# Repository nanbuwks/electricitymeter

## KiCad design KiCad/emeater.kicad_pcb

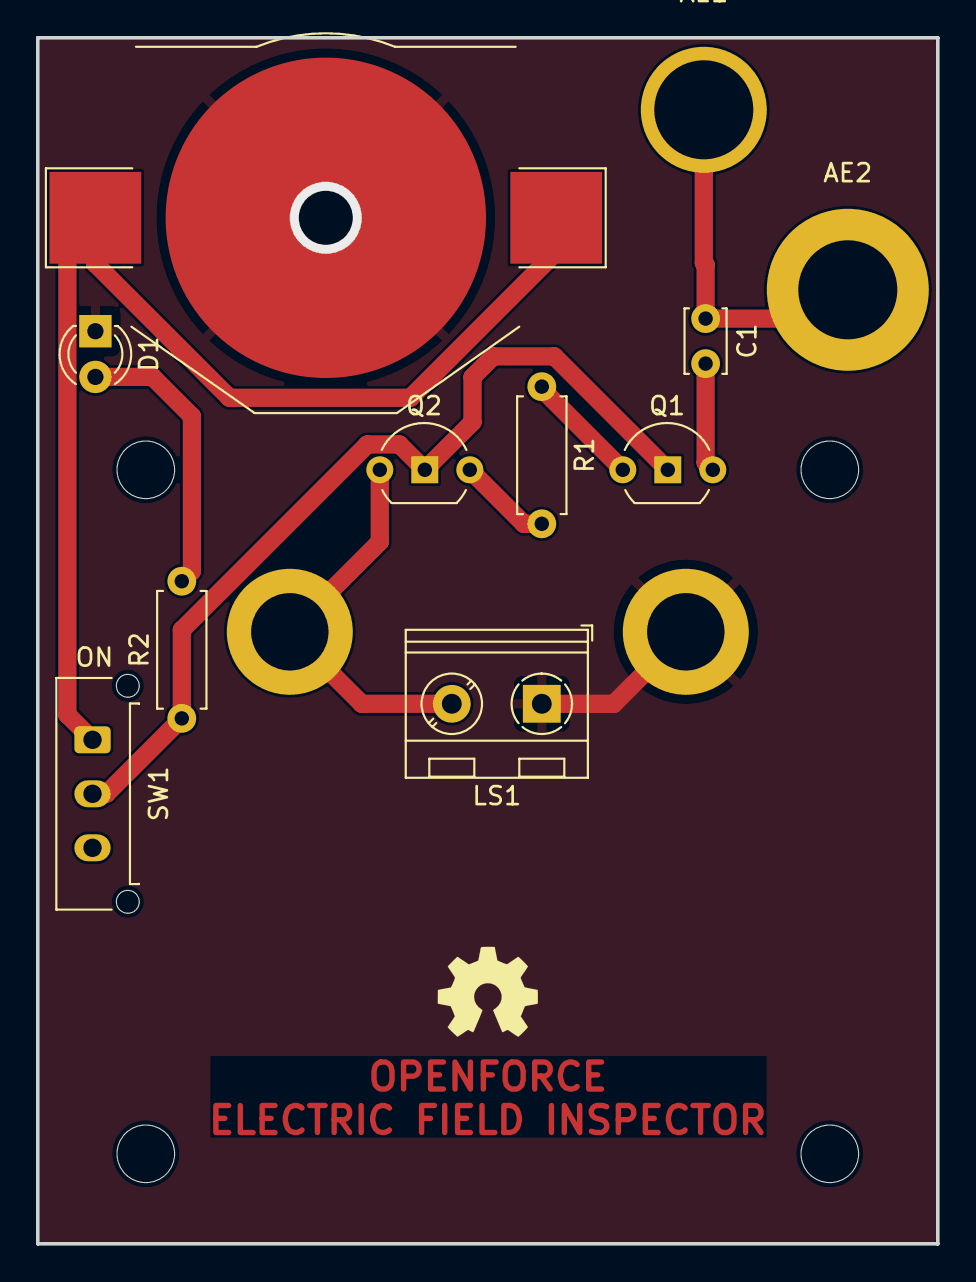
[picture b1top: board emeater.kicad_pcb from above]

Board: 2 copper layers, 50.0 x 67.0 mm, 13 parts (0 on the bottom side), 9 nets.

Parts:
AE1, AE2: Antenna; MountingHole_5.5mm_Pad
BT1: Battery_Cell; BatteryHolder_Keystone_3002_1x2032
C1: 0.1uF; C_Disc_D3.4mm_W2.1mm_P2.50mm
D1: LED; LED_D3.0mm
LS1: Earphone; TerminalBlock_RND_205-00045_1x02_P5.00mm_Horizontal
MES1: Ammeter_AC; 2x1_7.62mmScrewTerminal
OSHW: 1.1; OSHW_LOGL_SYLK_5mm
Q1, Q2: NPN; TO-92_Inline_Wide
R1, R2: 2.2k; R_Axial_DIN0207_L6.3mm_D2.5mm_P7.62mm_Horizontal
SW1: SW_SPDT; Molex_Micro-Fit_3.0_43650-0315_1x03_P3.00mm_Vertical

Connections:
GND: BT1.2 (-), D1.1 (K), LS1.1 (-), MES1.1
unnamed: AE1.1 (A), AE2.1 (A), C1.1
unnamed: BT1.1 (+), SW1.1 (A)
unnamed: D1.2 (A), R2.2
unnamed: LS1.2 (+), MES1.2, Q2.3 (E)
unnamed: C1.2, Q1.2 (B)
unnamed: Q1.1 (C), Q2.1 (C), R2.1, SW1.2 (B)
unnamed: Q1.3 (E), R1.1
unnamed: Q2.2 (B), R1.2
